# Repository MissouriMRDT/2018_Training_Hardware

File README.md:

# 2018_Training_Hardware
The Repo used for the 2018 DiveBoard Trainin

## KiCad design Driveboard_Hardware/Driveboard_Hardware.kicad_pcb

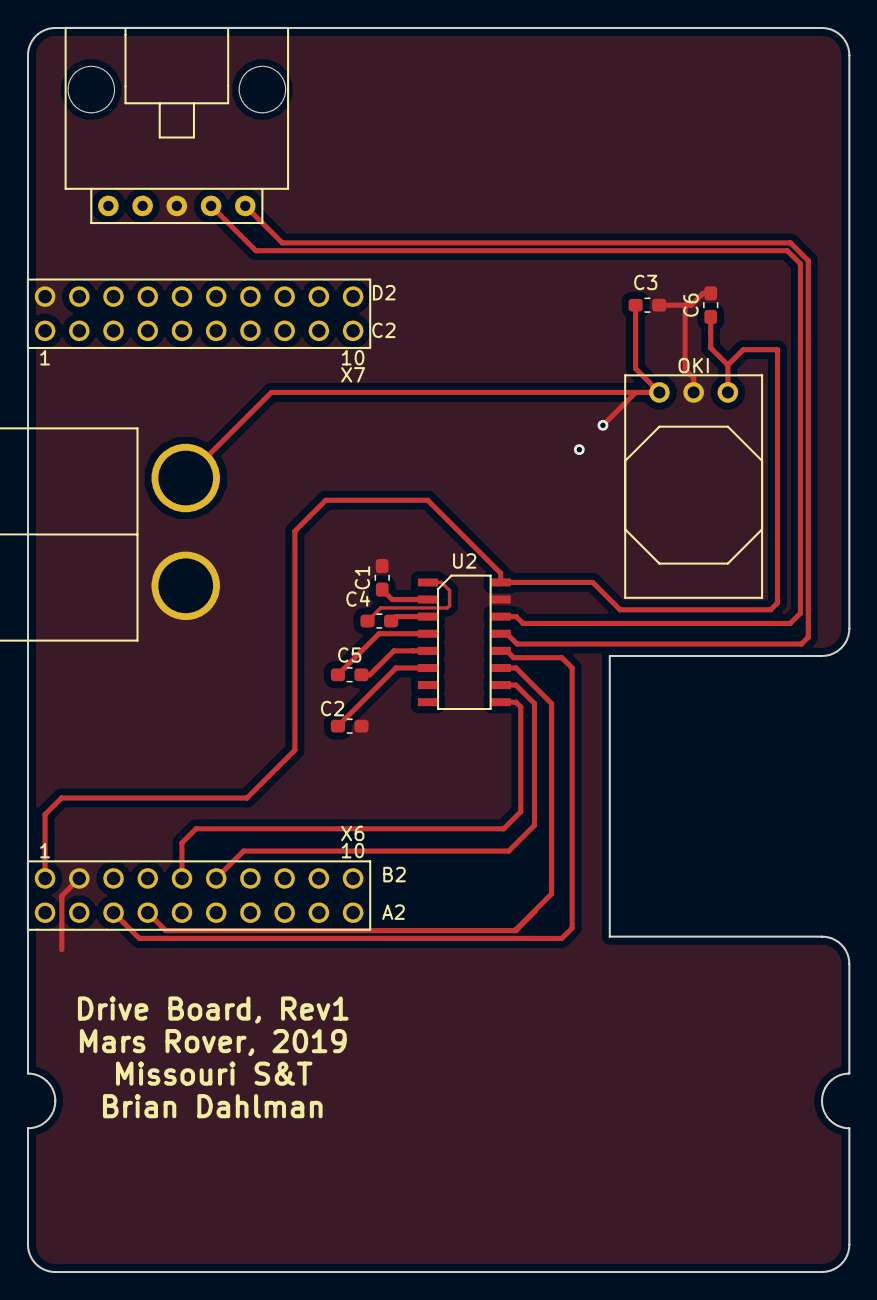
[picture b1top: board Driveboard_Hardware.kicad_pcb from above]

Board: 2 copper layers, 61.0 x 92.3 mm, 11 parts (0 on the bottom side), 15 nets.

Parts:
C1, C2, C4, C5: .1uF; C_0603_1608Metric_Pad1.05x0.95mm_HandSolder
C3, C6: 10uF; C_0603_1608Metric_Pad1.05x0.95mm_HandSolder
Conn1: AndersonPP; Anderson_2_Horisontal_Side_by_Side
Conn2: Molex_SL_05; MOLEX_SL_05_Horizontal
U1: TM4C129E_Launchpad; TM4C129E_Launchpad_X7
U2: MAX_3232; SOIC_16_3.9x9.9mm_Pitch1.27mm
U3: OKI; OKI_Horizontal

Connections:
+5V: C6.1, U1.+5V, U2.16, U3.3
/+12V: C3.1, Conn1.2, U3.1
GND: C1.2, C2.2, C3.2, C6.2, Conn1.1, Conn2.3, U1.GND, U2.15, U3.2
unnamed: C1.1, U2.2
unnamed: C2.1, U2.6
unnamed: C4.1, U2.1
unnamed: C4.2, U2.3
unnamed: C5.1, U2.4
unnamed: C5.2, U2.5
RX_1_IC: U1.PP0, U2.12
RX_1_SL: Conn2.5, U2.13
RX_2_IC: U1.PK0, U2.9
TX_1_IC: U1.PP1, U2.11
TX_1_SL: Conn2.4, U2.14
TX_2_IC: U1.PK1, U2.10

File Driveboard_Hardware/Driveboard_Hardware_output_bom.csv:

"Id";"Designator";"Package";"Quantity";"Designation";"Supplier and ref";
1;"C1,C2,C4,C5";"C_0603_1608Metric_Pad1.05x0.95mm_HandSolder";4;".1uF";;;
2;"C3,C6";"C_0603_1608Metric_Pad1.05x0.95mm_HandSolder";2;"10uF";;;
3;"Conn1";"Anderson_2_Horisontal_Side_by_Side";1;"AndersonPP";;;
4;"Conn2,Conn3";"MOLEX_SL_05_Horizontal";2;"Molex_SL_05";;;
5;"U1";"TM4C129E_Launchpad_X7";1;"TM4C129E_Launchpad";;;
6;"U2";"SOIC_16_3.9x9.9mm_Pitch1.27mm";1;"MAX_3232";;;
7;"U3";"OKI_Horizontal";1;"OKI";;;

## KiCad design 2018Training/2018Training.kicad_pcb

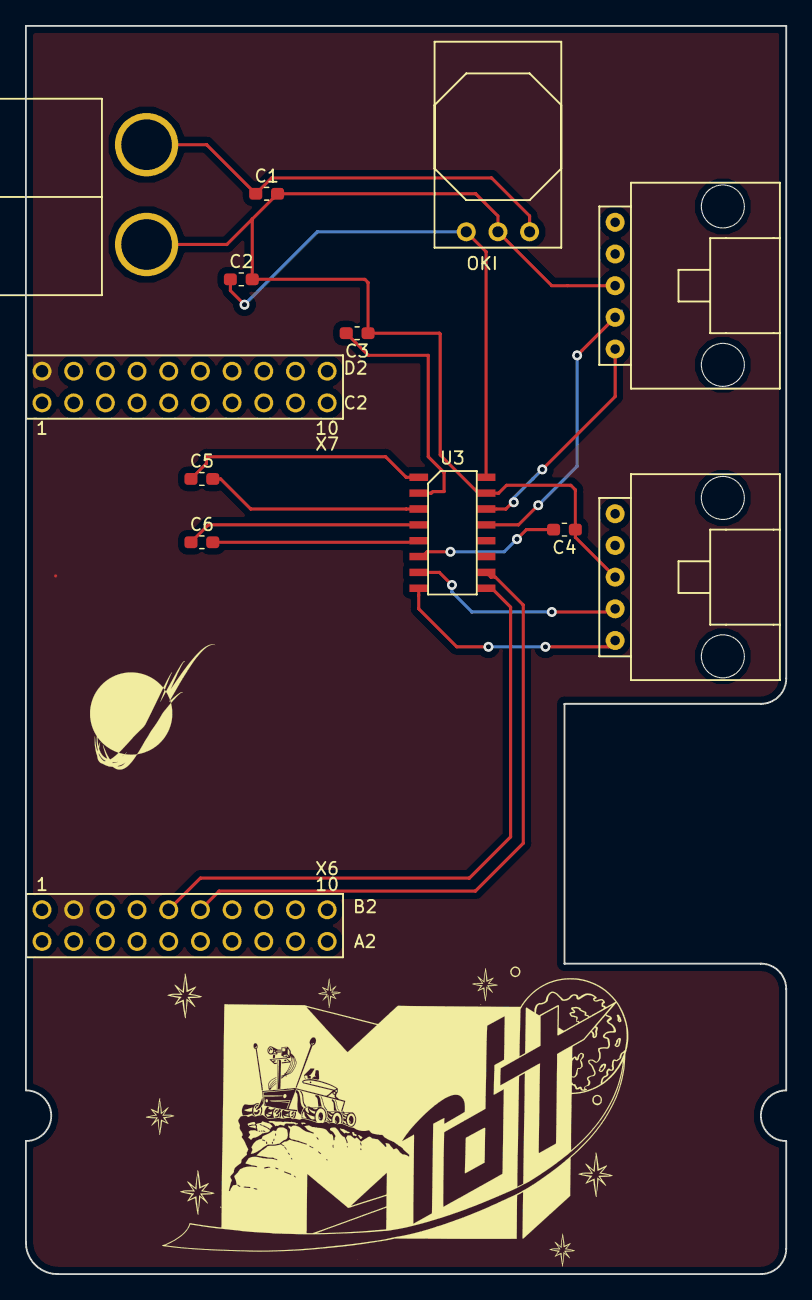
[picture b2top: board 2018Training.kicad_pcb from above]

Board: 2 copper layers, 61.0 x 100.1 mm, 12 parts (0 on the bottom side), 15 nets.

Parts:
C1, C2: 1.0uF; C_0603_1608Metric_Pad1.05x0.95mm_HandSolder
C3, C4, C5, C6: .1uF; C_0603_1608Metric_Pad1.05x0.95mm_HandSolder
Conn1: AndersonPP; Anderson_2_Horisontal_Side_by_Side
Conn2, Conn3: Molex_SL_05; MOLEX_SL_05_Horizontal
U1: TM4C129E_Launchpad; TM4C129E_Launchpad_X7
U2: OKI; OKI_Horizontal
U3: MAX_3232; SOIC_16_3.9x9.9mm_Pitch1.27mm

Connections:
/Serial4: U1.PK0, U3.9
unnamed: C1.1, Conn1.2, U2.1
unnamed: C1.2, C2.2, C3.1, C4.1, Conn1.1, Conn2.3, Conn3.3, U2.2, U3.15
unnamed: C2.1, U1.+5V, U2.3, U3.16
unnamed: C3.2, U3.2
unnamed: C4.2, U3.6
unnamed: C5.1, U3.1
unnamed: C5.2, U3.3
unnamed: C6.1, U3.4
unnamed: C6.2, U3.5
unnamed: Conn2.4, U3.13
unnamed: Conn2.5, U3.14
unnamed: Conn3.4, U3.7
unnamed: Conn3.5, U3.8
unnamed: U1.PK1, U3.10

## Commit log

2018-09-15 Added Training Resources
2018-09-15 Added DriveBoard Block Diagram
2018-09-15 Added text file because i wanted to
2018-09-15 fixed typo
2018-09-15 Updated Text
2018-09-15 updated text to be more exciting
2018-09-15 added words and stuff
2018-09-15 Board Files n' Stuff
2018-09-15 Training
    Training
2018-09-15 Started Project and added library
2018-09-15 Created Schematic
2018-09-17 Created Driveboard Project
2018-09-17 Added .pro File
2018-09-17 Added 5pin SL Connector
2018-09-18 added TMAC129E
2018-09-18 changed text file
2018-09-18 changed something
2018-09-18 I didnt do anything
2018-09-18 Fixed Schematic for KiCAD 5.0
2018-09-18 Added Ground and 5V power flags
2018-09-20 wired the elements
2018-09-21 Created and layed out schematic
2018-09-21 Started Kicad Project
2018-09-21 Added power & MAX3232
2018-09-22 Work
    '
2018-09-22 Here's the working libraries
2018-09-22 Not sure what this is
2018-09-22 Ompleted Board
2018-09-22 Annotated Schematic
2018-09-27 Circuit Schematic
2018-09-27 driveboard schmatic design
    finished design
2018-09-27 Changed Footprint Mapping to KiCAD 5.0
2018-09-28 Completed schmatic and board layout
2018-09-28 add my name
2018-09-28 added gerber
2018-09-28 Added power filtering
2018-09-29 Layout
2018-09-29 Generated Gerbs and BOM
2018-09-29 Board Update
    Completed PCB board
2018-09-29 Finished Board Layout
    Finished board, gerbs,
2018-09-29 Updated File PCB
2018-09-29 made Drive Board
2018-09-29 Revision 4, finished board
2018-09-29 Did stuff
2018-09-29 Merged files from Master
2018-09-29 Revision 1
2018-09-29 Board Revised and Checked
2018-09-29 Made Boared
    Created the schematic
2018-09-29 Update
    Small changes
2018-09-29 Completed board layout
2018-09-29 Silkscreens
2018-09-29 Updated Gerbs
2018-09-29 Added Gerbs
2018-09-29 Completed board design
2018-09-29 I did shit
2018-09-29 Board Layout Completed
2018-09-30 Finished BOM
2018-09-30 Created Gerbs
2018-10-04 Generated Gerbs
2018-10-08 Added Text
2018-10-10 Add files via upload
    Testing uploading to Github
2018-10-11 Updated VIAs
2018-10-11 Changed Vias
2018-10-11 Added RDriveBoard Hardware
2018-10-22 Test Commit
2018-11-01 Created Training Software
2018-11-03 commented example code
2018-11-11 Added Serial Debugging
2018-11-12 Fixed Write Bug
